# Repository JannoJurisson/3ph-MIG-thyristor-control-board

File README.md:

# 3ph-MIG-thyristor-control-board
Control board for my DIY 3 phase MIG welder that uses six thyristors(SCR) for rectifying the output of a old, soviet era three phase isolation transformer (~5kW). 
Raspberry Pico board is used to monitor and control all the functions

## Board Specifications

| Feature | Description |
| :--- | :--- |
| **Power Input** | +24V DC |
| **Current Control** | Potentiometer adjustment for welding current.   |
| **Phase Monitoring** | Isolated inputs for all phases for missing phase detection. |
| **SCR Drive** | Isolated output for six SCRs via ferrite transformers (20KHz). |
| **High-Current Outputs** | Gas solenoid, Main Contactor, Auxiliary Output. |
| **Motor Drivers** | 2x `DRV8825` stepper motor drivers. |
| **User Inputs** | Gun trigger switch, ADC for wire speed/current pots. |
| **Expansion** | `I2C` connector for displays and peripherals. |
| **Special Feature**| Wire motor balancing for dual-motor setups (e.g., spool gun).|

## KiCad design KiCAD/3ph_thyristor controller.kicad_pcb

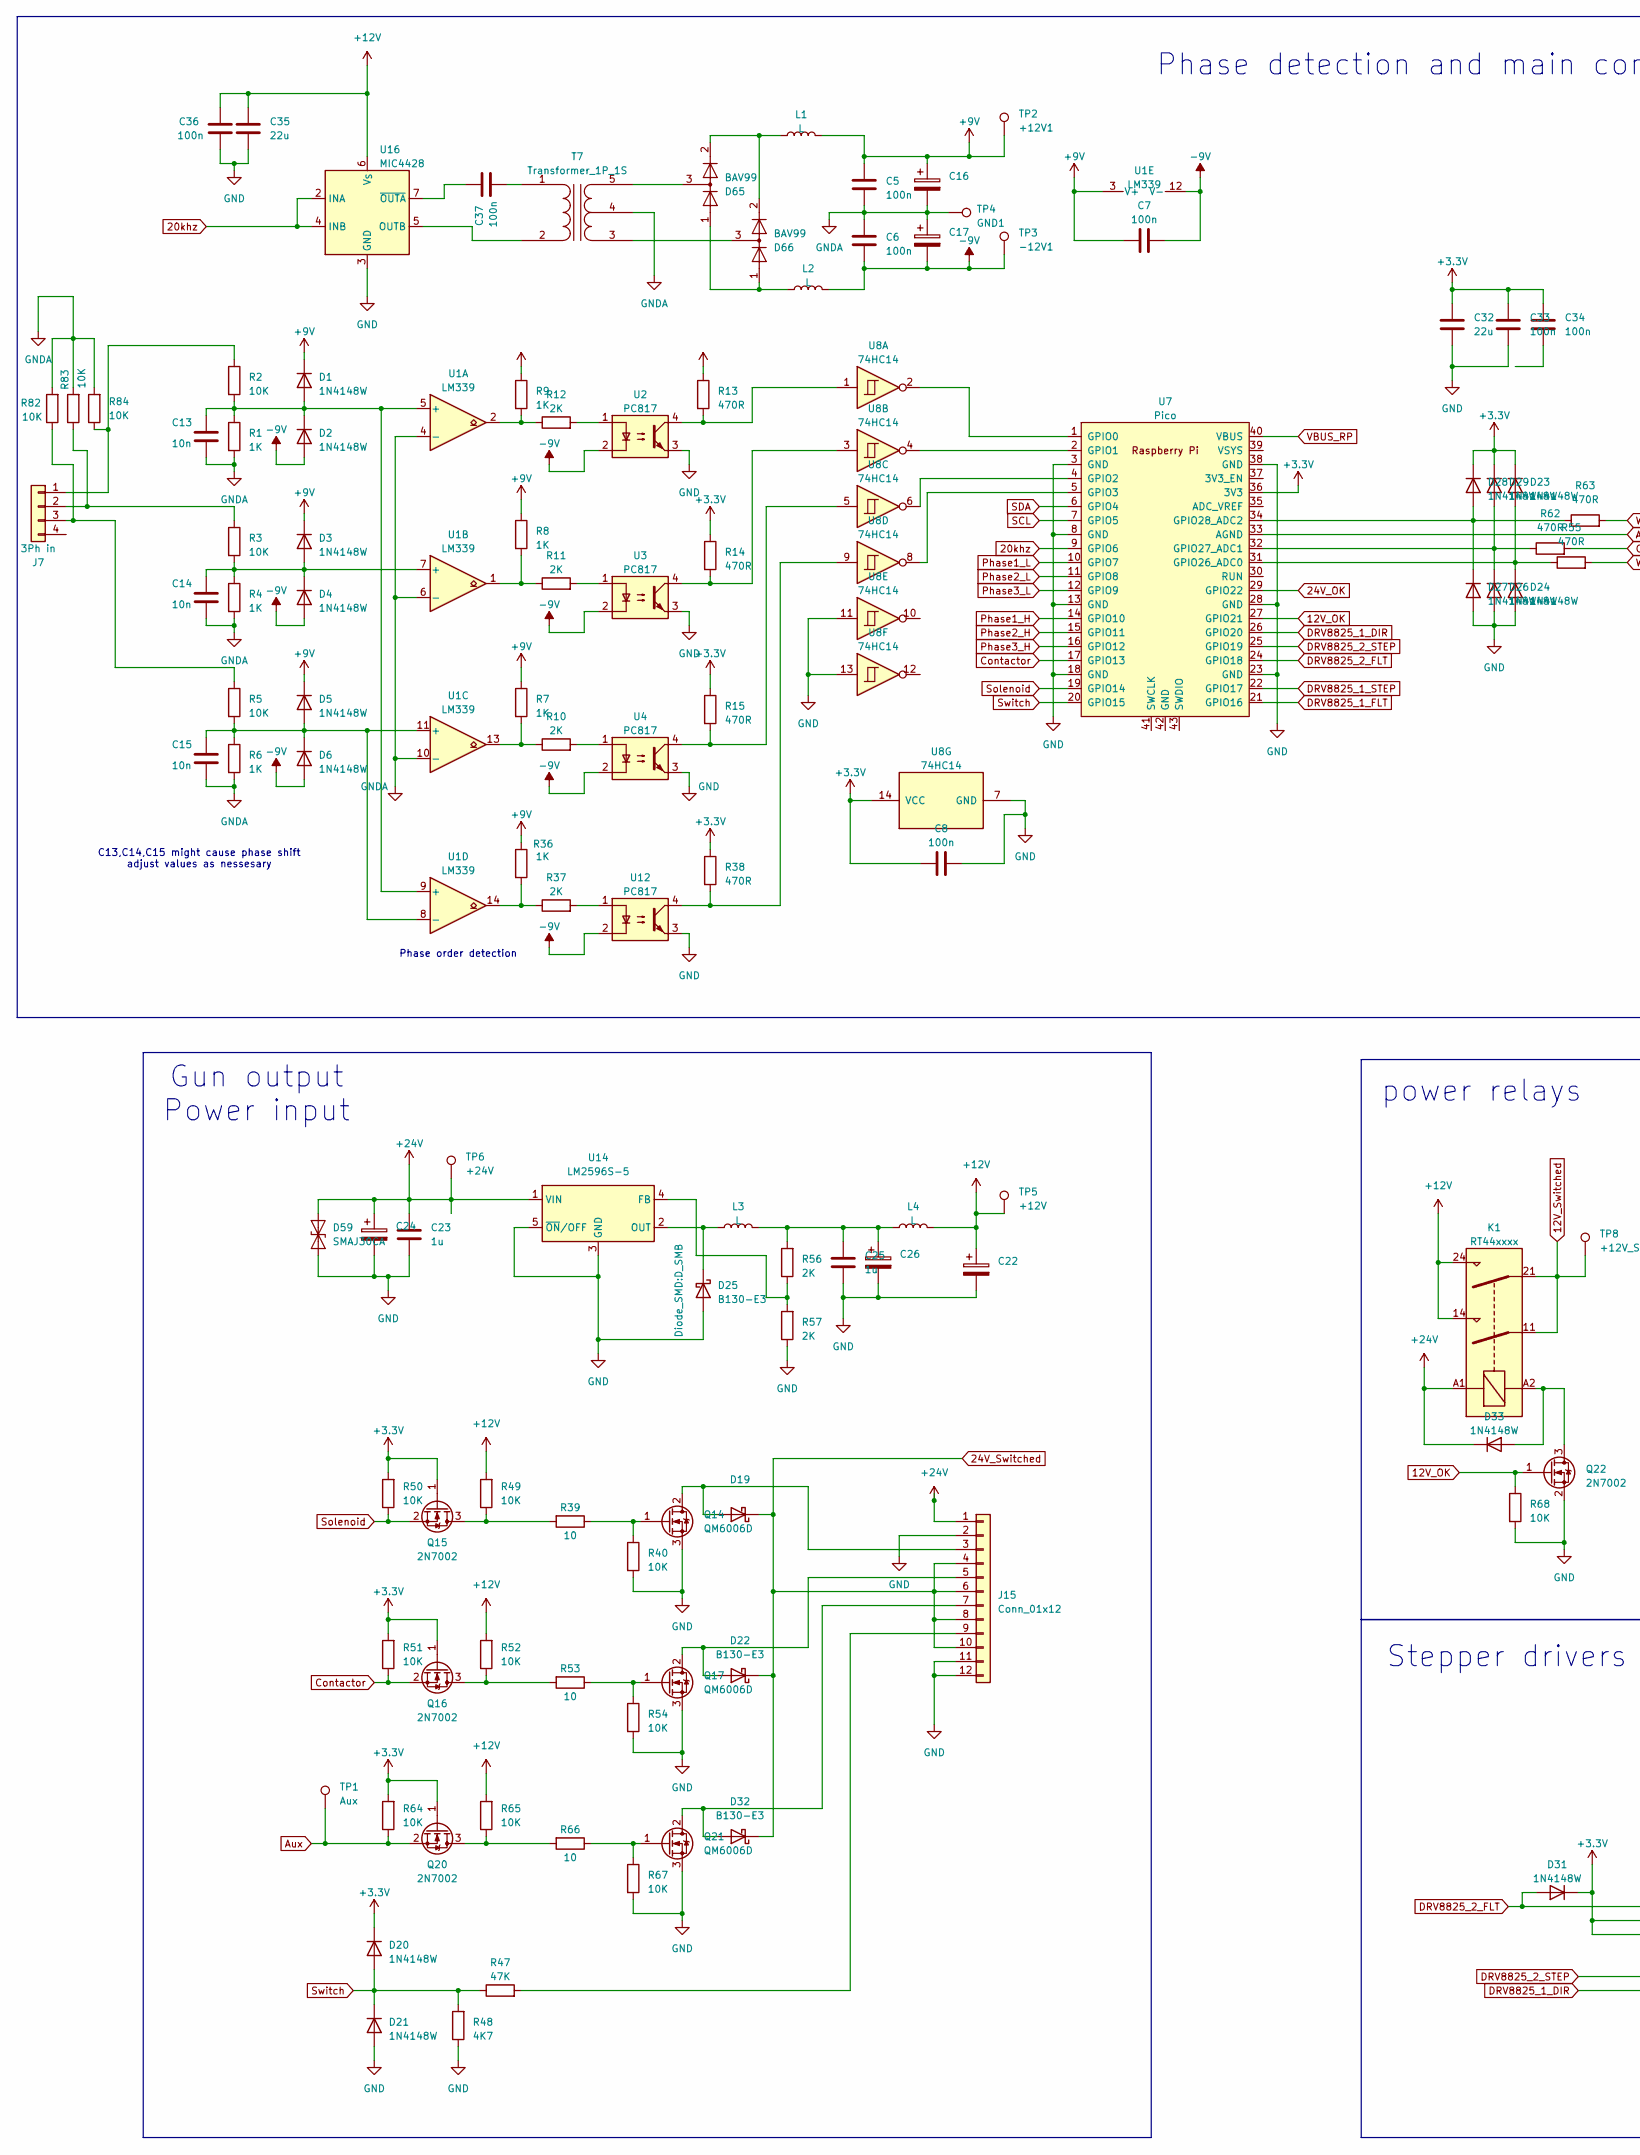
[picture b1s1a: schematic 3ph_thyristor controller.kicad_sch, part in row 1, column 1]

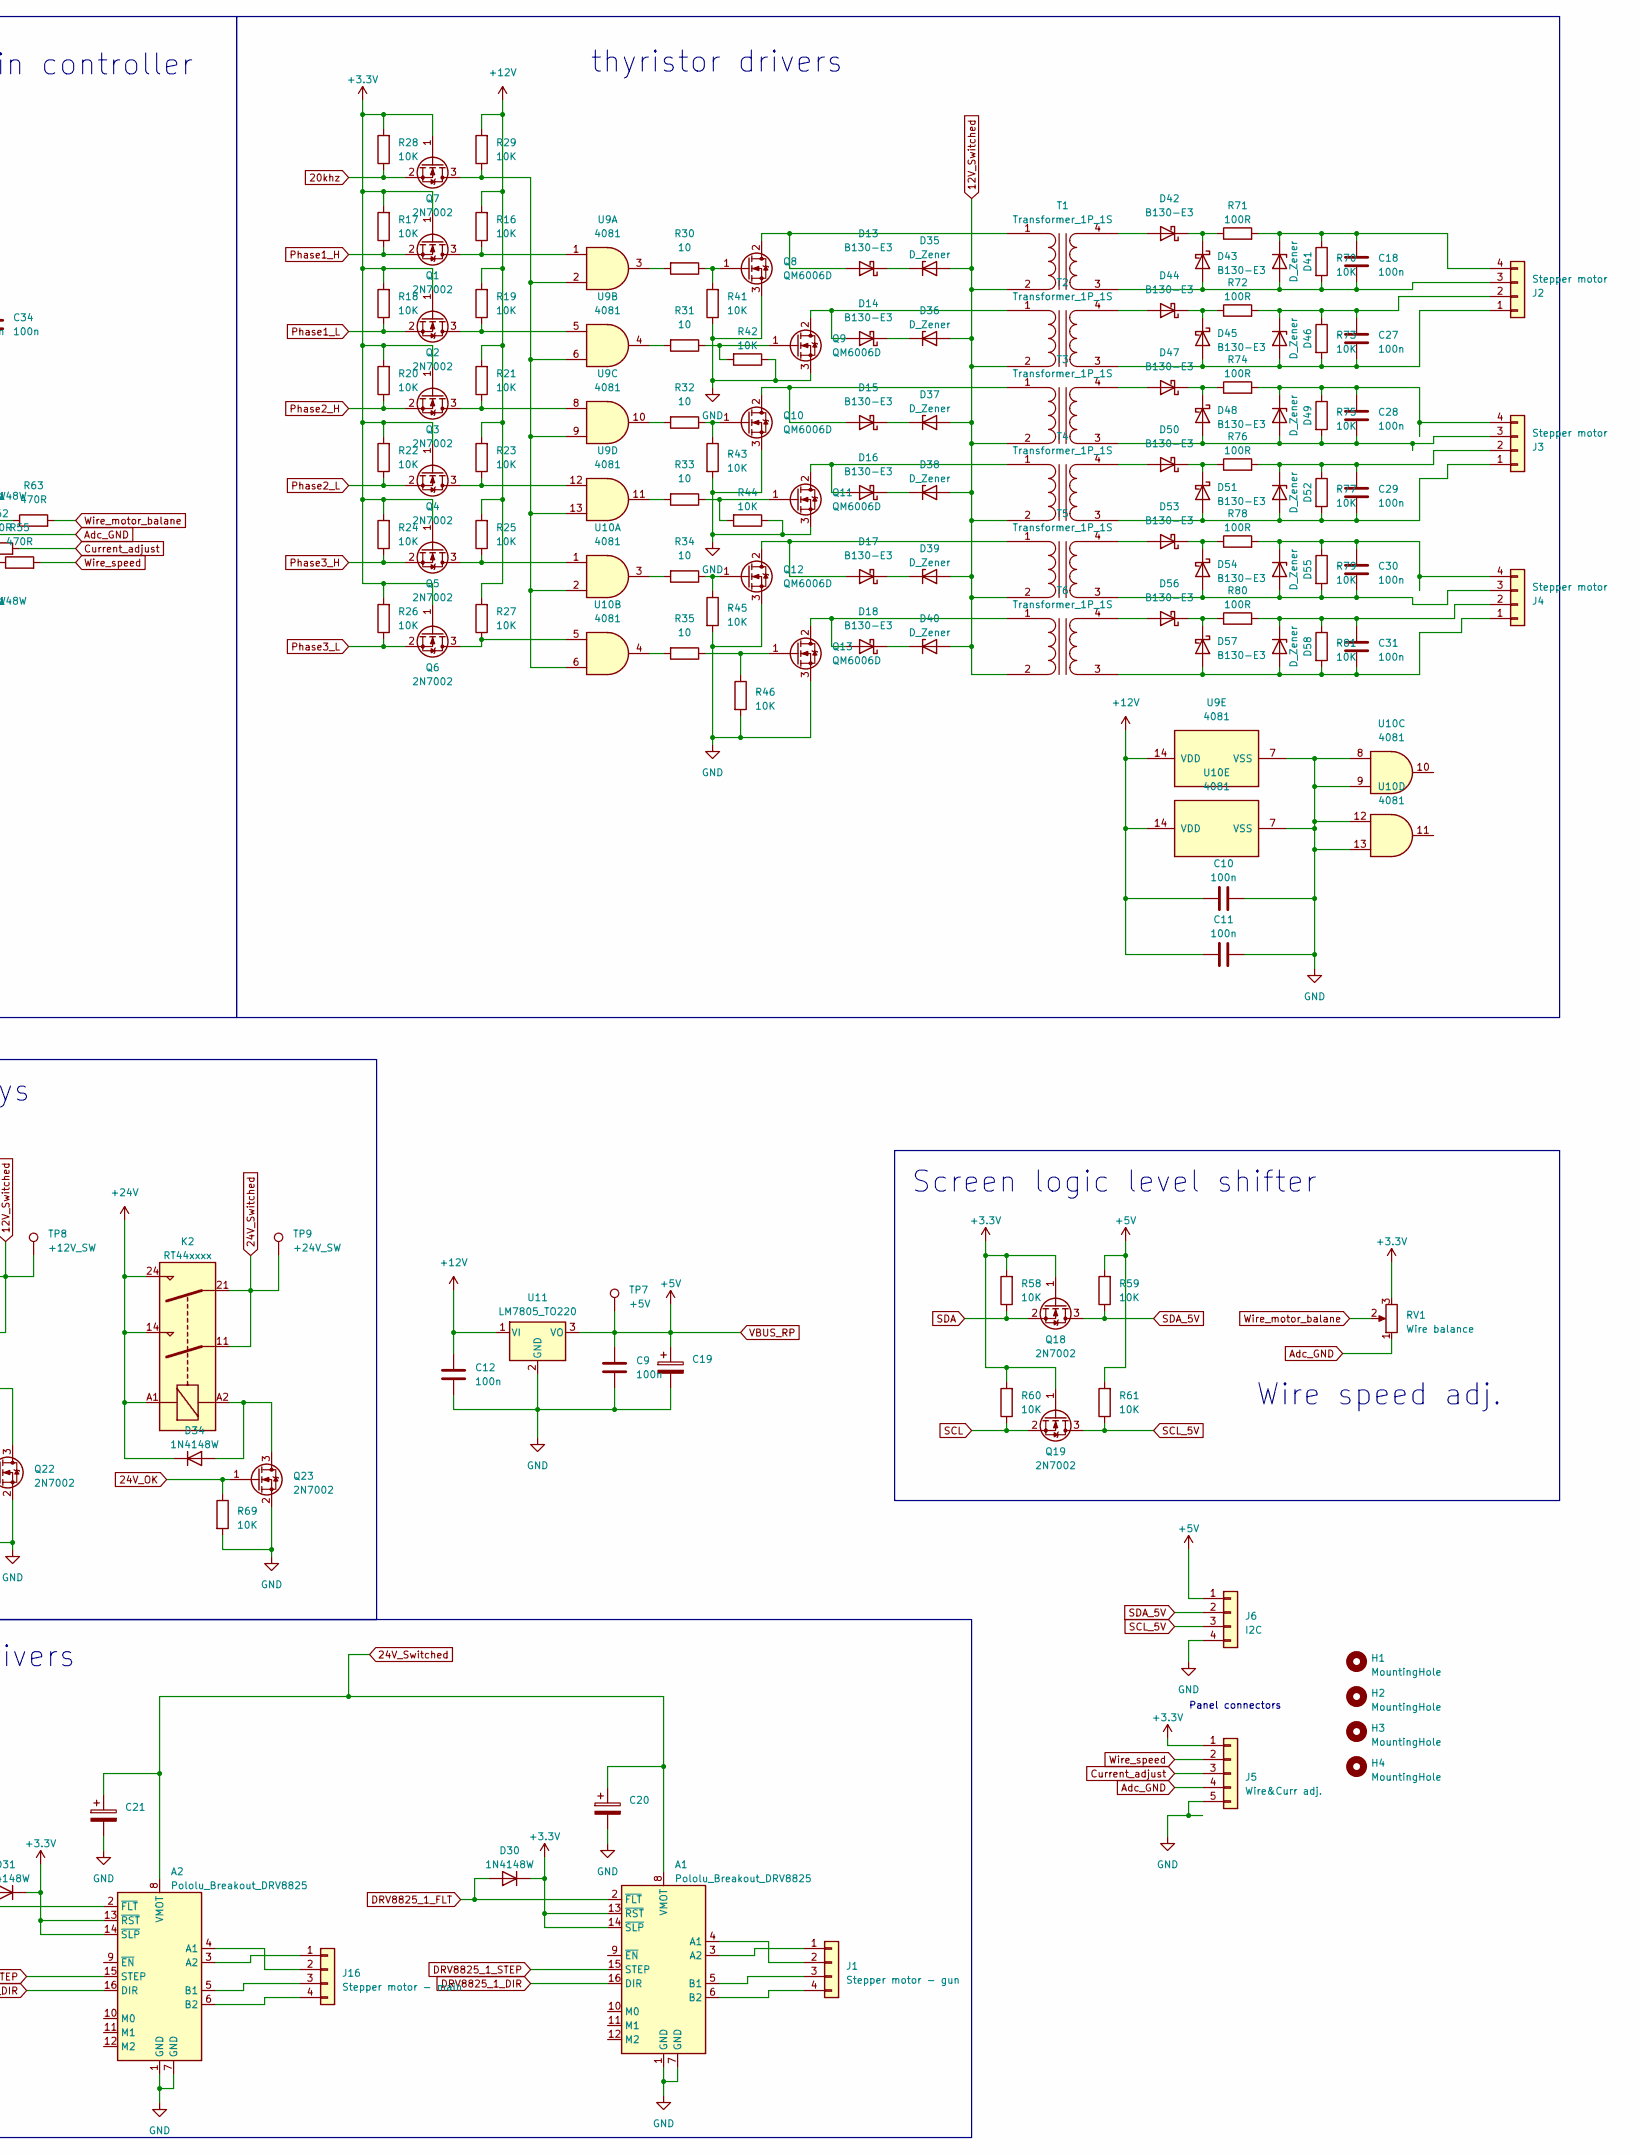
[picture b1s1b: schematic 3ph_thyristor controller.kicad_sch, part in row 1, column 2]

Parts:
A1, A2: Pololu_Breakout_DRV8825; Pololu_Breakout-16_15.2x20.3mm
C5, C6, C7, C8, C9, C10, C11, C12, C18, C27, C28, C29, C30, C31, C33, C34, C36, C37: 100n; C_0805_2012Metric
C13, C14, C15: 10n; C_0805_2012Metric
C16, C17, C19, C20, C21: C_Polarized; CP_Elec_10x10
C22, C24, C26: 220u; CP_Elec_10x10
C23, C25: 1u; C_1206_3216Metric
C32, C35: 22u; C_0805_2012Metric
D1, D2, D3, D4, D5, D6, D20, D21, D23, D24, D26, D27, D28, D29, D30, D31, D33, D34: 1N4148W; D_MiniMELF
D13, D14, D15, D16, D17, D18, D19, D22, D32, D42, D43, D44, D45, D47, D48, D50, D51, D53, D54, D56, D57: B130-E3; D_SMA
D25: B130-E3; D_SMB
D35, D36, D37, D38, D39, D40, D41, D46, D49, D52, D55, D58: D_Zener; D_SMA
D59: SMAJ30CA; D_SMC
D65, D66: BAV99; SOT-23
H1, H2, H3, H4: MountingHole; MountingHole_3.5mm
J1: Stepper motor - gun; PhoenixContact_MSTBA_2,5_4-G_1x04_P5.00mm_Horizontal
J2, J3, J4: Stepper motor; PhoenixContact_MSTBA_2,5_4-G_1x04_P5.00mm_Horizontal
J5: Wire&Curr adj.; Molex_KK-254_AE-6410-05A_1x05_P2.54mm_Vertical
J6: I2C; Molex_KK-254_AE-6410-04A_1x04_P2.54mm_Vertical
J7: 3Ph in; PhoenixContact_MSTBA_2,5_4-G_1x04_P5.00mm_Horizontal
J15: Conn_01x12; PhoenixContact_MC_1,5_12-G-3.5_1x12_P3.50mm_Horizontal
J16: Stepper motor - main; PhoenixContact_MSTBA_2,5_4-G_1x04_P5.00mm_Horizontal
K1, K2: RT44xxxx; Relay_DPST_Schrack-RT2-FormA_RM5mm
L1, L2: L; L_1210_3225Metric_Pad1.42x2.65mm_HandSolder
L3, L4: L; L_Bourns_SRR1260
Q1, Q2, Q3, Q4, Q5, Q6, Q7, Q15, Q16, Q18, Q19, Q20, Q22, Q23: 2N7002; SOT-23
Q8, Q9, Q10, Q11, Q12, Q13, Q14, Q17, Q21: QM6006D; TO-252-2
R1, R4, R6, R7, R8, R9, R36: 1K; R_0805_2012Metric
R2, R3, R5, R16, R17, R18, R19, R20, R21, R22, R23, R24, R25, R26, R27, R28, R29, R40, R41, R42, R43, R44, R45, R46, R49, R50, R51, R52, R54, R58, R59, R60, R61, R64, R65, R67, R68, R69, R70, R73, R75, R77, R79, R81, R82, R83, R84: 10K; R_0805_2012Metric
R10, R11, R12, R37, R56, R57: 2K; R_0805_2012Metric
R13, R14, R15, R38, R55, R62, R63: 470R; R_0805_2012Metric
R30, R31, R32, R33, R34, R35, R39, R53, R66: 10; R_0805_2012Metric
R47: 47K; R_0805_2012Metric
R48: 4K7; R_0805_2012Metric
R71, R72, R74, R76, R78, R80: 100R; R_0805_2012Metric
RV1: Wire balance; Potentiometer_ACP_CA9-V10_Vertical_Hole
T1, T2, T3, T4, T5, T6, T7: Transformer_1P_1S; Transformer_Toroid_Horizontal_D18.0mm
TP1: Aux; TestPoint_Pad_D2.0mm
TP2: +12V1; TestPoint_Pad_D2.0mm
TP3: -12V1; TestPoint_Pad_D2.0mm
TP4: GND1; TestPoint_Pad_D2.0mm
TP5: +12V; TestPoint_Pad_D2.0mm
TP6: +24V; TestPoint_Pad_D2.0mm
TP7: +5V; TestPoint_Pad_D2.0mm
TP8: +12V_SW; TestPoint_Pad_D2.0mm
TP9: +24V_SW; TestPoint_Pad_D2.0mm
U1: LM339; SOIC-14_3.9x8.7mm_P1.27mm
U2, U3, U4, U12: PC817; DIP-4_W7.62mm_SMDSocket_SmallPads
U7: Pico; RPi_Pico_SMD_TH
U8: 74HC14; SOIC-14_3.9x8.7mm_P1.27mm
U9, U10: 4081; SOIC-14_3.9x8.7mm_P1.27mm
U11: LM7805_TO220; TO-252-3_TabPin2
U14: LM2596S-5; TO-263-5_TabPin3
U16: MIC4428; SOIC-8_3.9x4.9mm_P1.27mm

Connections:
12V_OK: Q22.1 (G), R68.1, U7.27 (GPIO21)
12V_Switched: D35.2 (A), D36.2 (A), D37.2 (A), D38.2 (A), D39.2 (A), D40.2 (A), K1.11, K1.21, T1.2 (AB), T2.2 (AB), T3.2 (AB), T4.2 (AB), T5.2 (AB), T6.2 (AB), TP8.1
20khz: Q7.2 (S), R28.1, U7.9 (GPIO6), U16.2 (INA), U16.4 (INB)
24V_OK: Q23.1 (G), R69.1, U7.29 (GPIO22)
24V_Switched: A1.8 (VMOT), A2.8 (VMOT), C20.1, C21.1, D19.1 (K), D22.1 (K), D32.1 (K), J15.4, J15.6, J15.8, J15.10, K2.11, K2.21, TP9.1
+3.3V: A1.13 (~RST), A1.14 (~SLP), A2.13 (~RST), A2.14 (~SLP), C8.1, C32.2, C33.2, C34.2, D20.1 (K), D23.1 (K), D28.1 (K), D29.1 (K), D30.1 (K), D31.1 (K), J5.1, Q1.1 (G), Q2.1 (G), Q3.1 (G), Q4.1 (G), Q5.1 (G), Q6.1 (G), Q7.1 (G), Q15.1 (G), Q16.1 (G), Q18.1 (G), Q19.1 (G), Q20.1 (G), R13.1, R14.1, R15.1, R17.2, R18.2, R20.2, R22.2, R24.2, R26.2, R28.2, R38.1, R50.2, R51.2, R58.2, R60.2, R64.2, RV1.3, U7.36 (3V3), U8.14 (VCC)
+9V: C5.1, C7.1, C16.1, D1.1 (K), D3.1 (K), D5.1 (K), L1.2, R7.1, R8.1, R9.1, R36.1, TP2.1, U1.3 (V+)
+12V: C10.1, C11.1, C12.2, C22.1, C35.2, C36.2, K1.14, K1.24, L4.2, R16.2, R19.2, R21.2, R23.2, R25.2, R27.2, R29.2, R49.2, R52.2, R65.2, TP5.1, U9.14 (VDD), U10.14 (VDD), U11.1 (VI), U16.6 (V_{S})
+24V: C23.2, C24.1, D33.1 (K), D34.1 (K), D59.2 (A2), J15.1, K1.A1, K2.14, K2.24, K2.A1, TP6.1, U14.1 (VIN)
-9V: C6.2, C7.2, C17.2, D2.2 (A), D4.2 (A), D6.2 (A), L2.2, TP3.1, U1.12 (V-), U2.2, U3.2, U4.2, U12.2
Adc_GND: J5.4, RV1.1, U7.33 (AGND)
Aux: Q20.2 (S), R64.1, TP1.1
Contactor: Q16.2 (S), R51.1, U7.17 (GPIO13)
Current_adjust: J5.3, R62.2
DRV8825_1_DIR: A1.16 (DIR), A2.16 (DIR), U7.26 (GPIO20)
DRV8825_1_FLT: A1.2 (~FLT), D30.2 (A), U7.21 (GPIO16)
DRV8825_1_STEP: A1.15 (STEP), U7.22 (GPIO17)
DRV8825_2_FLT: A2.2 (~FLT), D31.2 (A), U7.24 (GPIO18)
DRV8825_2_STEP: A2.15 (STEP), U7.25 (GPIO19)
GND: A1.1 (GND), A1.7 (GND), A2.1 (GND), A2.7 (GND), C8.2, C9.1, C10.2, C11.2, C12.1, C19.2, C20.2, C21.2, C22.2, C23.1, C24.2, C25.1, C26.2, C32.1, C33.1, C35.1, C36.1, D21.2 (A), D24.2 (A), D25.2 (A), D26.2 (A), D27.2 (A), D59.1 (A1), J5.5, J6.4, J15.2, J15.11, J15.12, Q8.3 (S), Q9.3 (S), Q10.3 (S), Q11.3 (S), Q12.3 (S), Q13.3 (S), Q14.3 (S), Q17.3 (S), Q21.3 (S), Q22.2 (S), Q23.2 (S), R40.2, R41.1, R42.1, R43.2, R44.1, R45.2, R46.2, R48.1, R54.2, R57.1, R67.2, R68.2, R69.2, U2.3, U3.3, U4.3, U7.3 (GND), U7.8 (GND), U7.13 (GND), U7.18 (GND), U7.23 (GND), U7.28 (GND), U7.38 (GND), U8.7 (GND), U8.11, U8.13, U9.7 (VSS), U10.7 (VSS), U10.8, U10.9, U10.12, U10.13, U11.2 (GND), U12.3, U14.3 (GND), U14.5 (~ON/OFF), U16.3 (GND)
GNDA: C5.2, C6.1, C13.2, C14.2, C15.2, C16.2, C17.1, R1.2, R4.2, R6.2, R82.2, R83.2, R84.2, T7.4 (SA), TP4.1, U1.4 (-), U1.6 (-), U1.10 (-)
unnamed: A1.4 (A1), J1.2
unnamed: A1.3 (A2), J1.1
unnamed: A1.5 (B1), J1.3
unnamed: A1.6 (B2), J1.4
unnamed: A2.4 (A1), J16.2
unnamed: A2.3 (A2), J16.1
unnamed: A2.5 (B1), J16.3
unnamed: A2.6 (B2), J16.4
unnamed: C25.2, C26.1, L3.2, L4.1, R56.2
unnamed: C13.1, D1.2 (A), D2.1 (K), R1.1, R2.2, U1.5 (+), U1.9 (+)
unnamed: C14.1, D3.2 (A), D4.1 (K), R3.2, R4.1, U1.7 (+)
unnamed: C15.1, D5.2 (A), D6.1 (K), R5.2, R6.1, U1.8 (-), U1.11 (+)
unnamed: D13.2 (A), Q8.2 (D), T1.1 (AA)
unnamed: D13.1 (K), D35.1 (K)
unnamed: D14.2 (A), Q9.2 (D), T2.1 (AA)
unnamed: D14.1 (K), D36.1 (K)
unnamed: D15.2 (A), Q10.2 (D), T3.1 (AA)
unnamed: D15.1 (K), D37.1 (K)
unnamed: D16.2 (A), Q11.2 (D), T4.1 (AA)
unnamed: D16.1 (K), D38.1 (K)
unnamed: D17.2 (A), Q12.2 (D), T5.1 (AA)
unnamed: D17.1 (K), D39.1 (K)
unnamed: D18.2 (A), Q13.2 (D), T6.1 (AA)
unnamed: D18.1 (K), D40.1 (K)
unnamed: D19.2 (A), J15.3, Q14.2 (D)
unnamed: D22.2 (A), J15.5, Q17.2 (D)
unnamed: D23.2 (A), D24.1 (K), R55.1, U7.31 (GPIO26_ADC0)
unnamed: D25.1 (K), L3.1, U14.2 (OUT)
unnamed: D26.1 (K), D29.2 (A), R62.1, U7.32 (GPIO27_ADC1)
unnamed: D27.1 (K), D28.2 (A), R63.1, U7.34 (GPIO28_ADC2)
unnamed: D32.2 (A), J15.7, Q21.2 (D)
unnamed: D33.2 (A), K1.A2, Q22.3 (D)
unnamed: D34.2 (A), K2.A2, Q23.3 (D)
unnamed: C18.1, D41.2 (A), D43.2 (A), J2.3, R70.2, T1.3 (SA)
unnamed: C18.2, D41.1 (K), J2.4, R70.1, R71.2
unnamed: D42.2 (A), T1.4 (SB)
unnamed: D42.1 (K), D43.1 (K), R71.1
unnamed: D44.2 (A), T2.4 (SB)
unnamed: D44.1 (K), D45.1 (K), R72.1
unnamed: C27.1, D45.2 (A), D46.2 (A), J2.1, R73.2, T2.3 (SA)
unnamed: C27.2, D46.1 (K), J2.2, R72.2, R73.1
unnamed: D47.2 (A), T3.4 (SB)
unnamed: D47.1 (K), D48.1 (K), R74.1
unnamed: C28.1, D48.2 (A), D49.2 (A), J3.3, R75.2, T3.3 (SA)
unnamed: C28.2, D49.1 (K), J3.4, R74.2, R75.1
unnamed: D50.2 (A), T4.4 (SB)
unnamed: D50.1 (K), D51.1 (K), R76.1
unnamed: C29.1, D51.2 (A), D52.2 (A), J3.1, R77.2, T4.3 (SA)
unnamed: C29.2, D52.1 (K), J3.2, R76.2, R77.1
unnamed: D53.2 (A), T5.4 (SB)
unnamed: D53.1 (K), D54.1 (K), R78.1
unnamed: C30.1, D54.2 (A), D55.2 (A), J4.3, R79.2, T5.3 (SA)
unnamed: C30.2, D55.1 (K), J4.4, R78.2, R79.1
unnamed: D56.2 (A), T6.4 (SB)
unnamed: D56.1 (K), D57.1 (K), R80.1
unnamed: C31.1, D57.2 (A), D58.2 (A), J4.1, R81.2, T6.3 (SA)
unnamed: C31.2, D58.1 (K), J4.2, R80.2, R81.1
unnamed: D65.2 (A), D66.2 (A), L1.1
unnamed: D65.1 (K), D66.1 (K), L2.1
unnamed: D66.3 (K), T7.3 (SA)
unnamed: J7.1, R2.1, R84.1
unnamed: J7.2, R3.1, R83.1
unnamed: J7.3, R5.1, R82.1
unnamed: J15.9, R47.2
unnamed: Q1.3 (D), R16.1, U9.1
unnamed: Q2.3 (D), R19.1, U9.5
unnamed: Q3.3 (D), R21.1, U9.8
unnamed: Q4.3 (D), R23.1, U9.12
unnamed: Q5.3 (D), R25.1, U10.1
unnamed: Q6.3 (D), R27.1, U10.5
unnamed: Q7.3 (D), R29.1, U9.2, U9.6, U9.9, U9.13, U10.2, U10.6
unnamed: Q8.1 (G), R30.1, R41.2
unnamed: Q9.1 (G), R31.1, R42.2
unnamed: Q10.1 (G), R32.1, R43.1
unnamed: Q11.1 (G), R33.1, R44.2
unnamed: Q12.1 (G), R34.1, R45.1
unnamed: Q13.1 (G), R35.1, R46.1
unnamed: Q14.1 (G), R39.1, R40.1
unnamed: Q15.3 (D), R39.2, R49.1
unnamed: Q16.3 (D), R52.1, R53.2
unnamed: Q17.1 (G), R53.1, R54.1
unnamed: Q20.3 (D), R65.1, R66.2
unnamed: Q21.1 (G), R66.1, R67.1
unnamed: R7.2, R10.1, U1.13
unnamed: R10.2, U4.1
unnamed: R8.2, R11.1, U1.1
unnamed: R11.2, U3.1
unnamed: R9.2, R12.1, U1.2
unnamed: R12.2, U2.1
unnamed: R13.2, U2.4, U8.1
unnamed: R14.2, U3.4, U8.3
unnamed: R15.2, U4.4, U8.5
unnamed: R30.2, U9.3
unnamed: R31.2, U9.4
unnamed: R32.2, U9.10
unnamed: R33.2, U9.11
unnamed: R34.2, U10.3
unnamed: R35.2, U10.4
unnamed: R36.2, R37.1, U1.14
unnamed: R37.2, U12.1
unnamed: R38.2, U8.9, U12.4
unnamed: C37.1, T7.1 (AA)
unnamed: T7.2 (AB), U16.5 (OUTB)
unnamed: D65.3 (K), T7.5 (SB)
unnamed: U7.1 (GPIO0), U8.2
unnamed: U7.2 (GPIO1), U8.4
unnamed: U7.4 (GPIO2), U8.6
unnamed: U7.5 (GPIO3), U8.8
unnamed: R56.1, R57.2, U14.4 (FB)
unnamed: C37.2, U16.7 (~OUTA)
Phase1_H: Q1.2 (S), R17.1, U7.14 (GPIO10)
Phase1_L: Q2.2 (S), R18.1, U7.10 (GPIO7)
Phase2_H: Q3.2 (S), R20.1, U7.15 (GPIO11)
Phase2_L: Q4.2 (S), R22.1, U7.11 (GPIO8)
Phase3_H: Q5.2 (S), R24.1, U7.16 (GPIO12)
Phase3_L: Q6.2 (S), R26.1, U7.12 (GPIO9)
SCL: Q19.2 (S), R60.1, U7.7 (GPIO5)
SCL_5V: J6.3, Q19.3 (D), R61.1
SDA: Q18.2 (S), R58.1, U7.6 (GPIO4)
SDA_5V: J6.2, Q18.3 (D), R59.1
Solenoid: Q15.2 (S), R50.1, U7.19 (GPIO14)
Switch: D20.2 (A), D21.1 (K), R47.1, R48.2, U7.20 (GPIO15)
VBUS_RP: C9.2, C19.1, J6.1, R59.2, R61.2, TP7.1, U7.40 (VBUS), U11.3 (VO)
Wire_motor_balane: R63.2, RV1.2
Wire_speed: J5.2, R55.2

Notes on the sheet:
Phase order detection
Gun output Power input
Phase detection and main controller
Screen logic level shifter
power relays
Wire speed adj.
thyristor drivers
C13,C14,C15 might cause phase shift adjust values as nessesary
Stepper drivers
Panel connectors

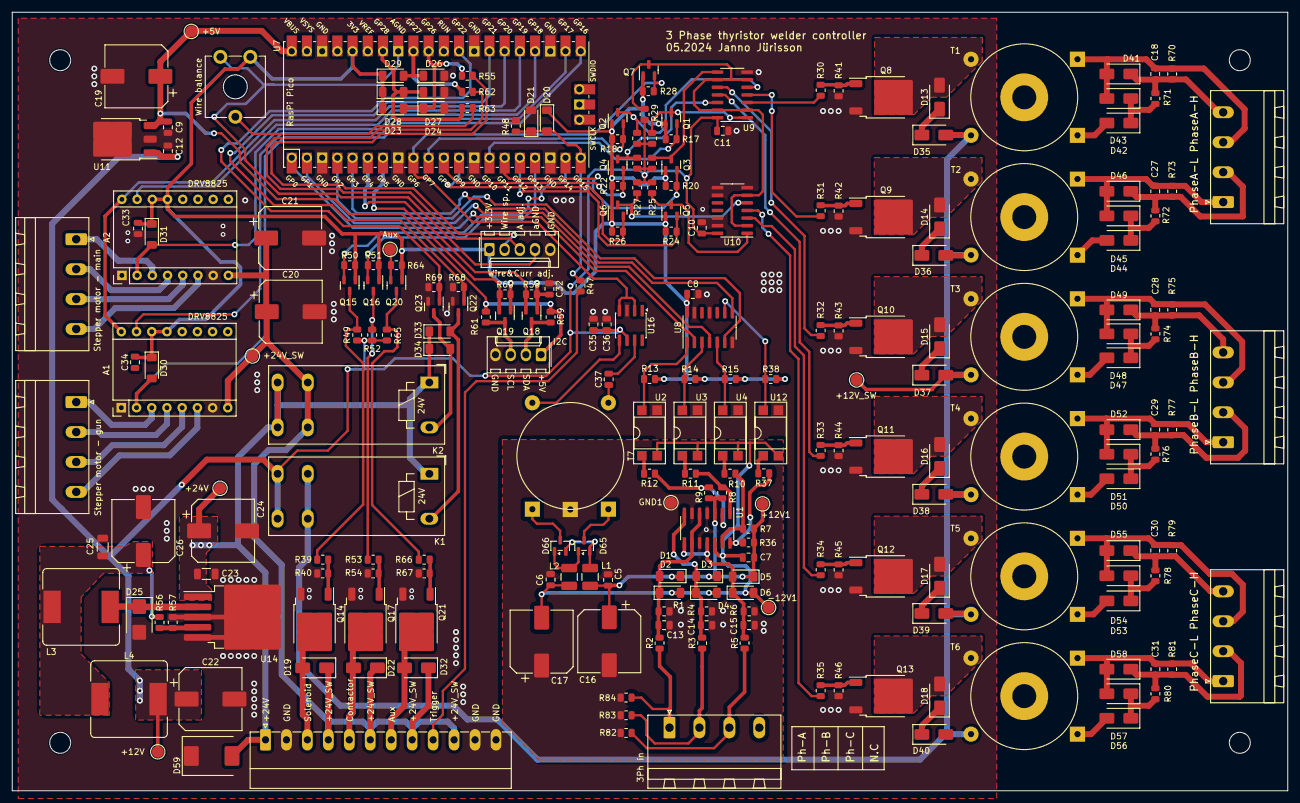
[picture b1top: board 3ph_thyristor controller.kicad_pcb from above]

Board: 2 copper layers, 213.0 x 130.0 mm, 245 parts (0 on the bottom side), 146 nets.
